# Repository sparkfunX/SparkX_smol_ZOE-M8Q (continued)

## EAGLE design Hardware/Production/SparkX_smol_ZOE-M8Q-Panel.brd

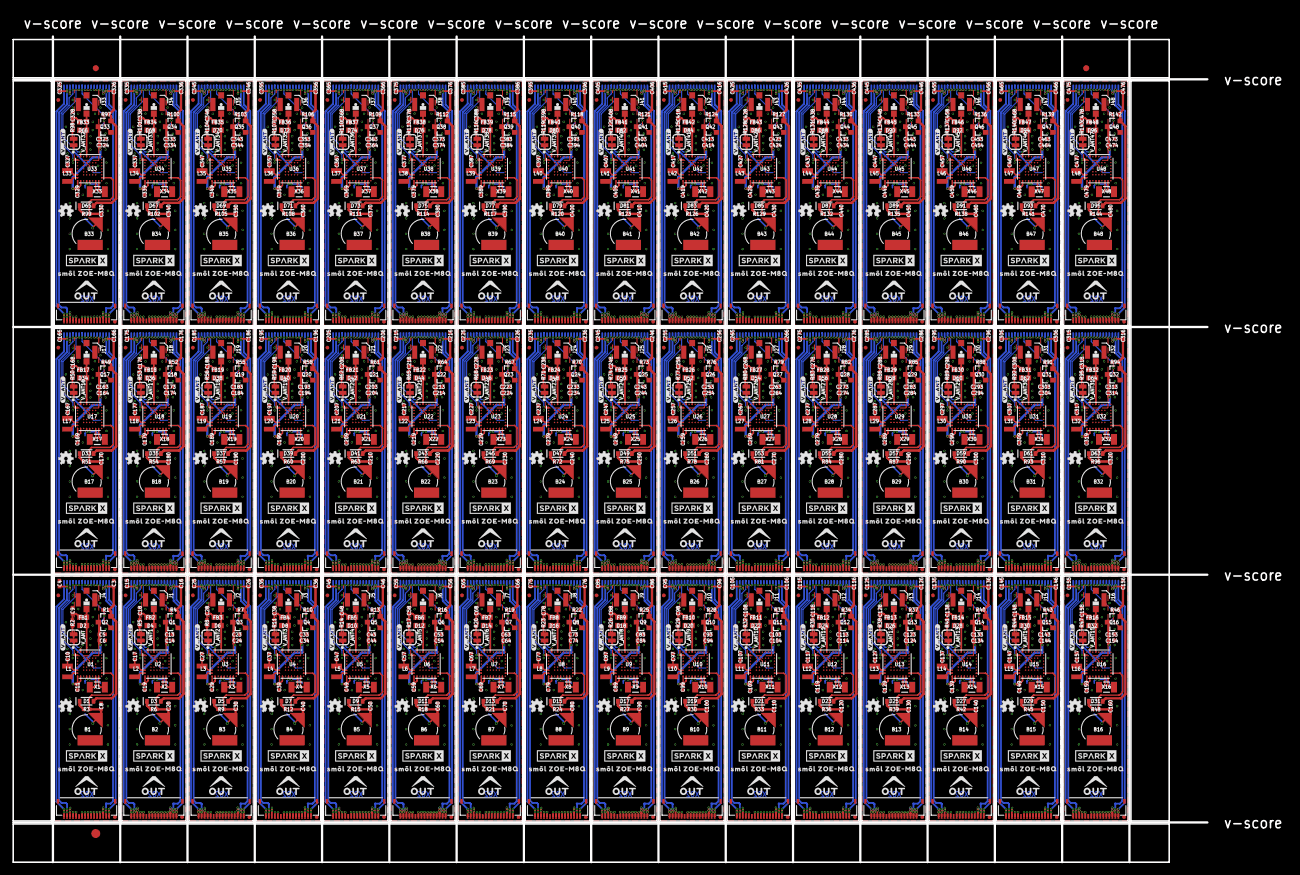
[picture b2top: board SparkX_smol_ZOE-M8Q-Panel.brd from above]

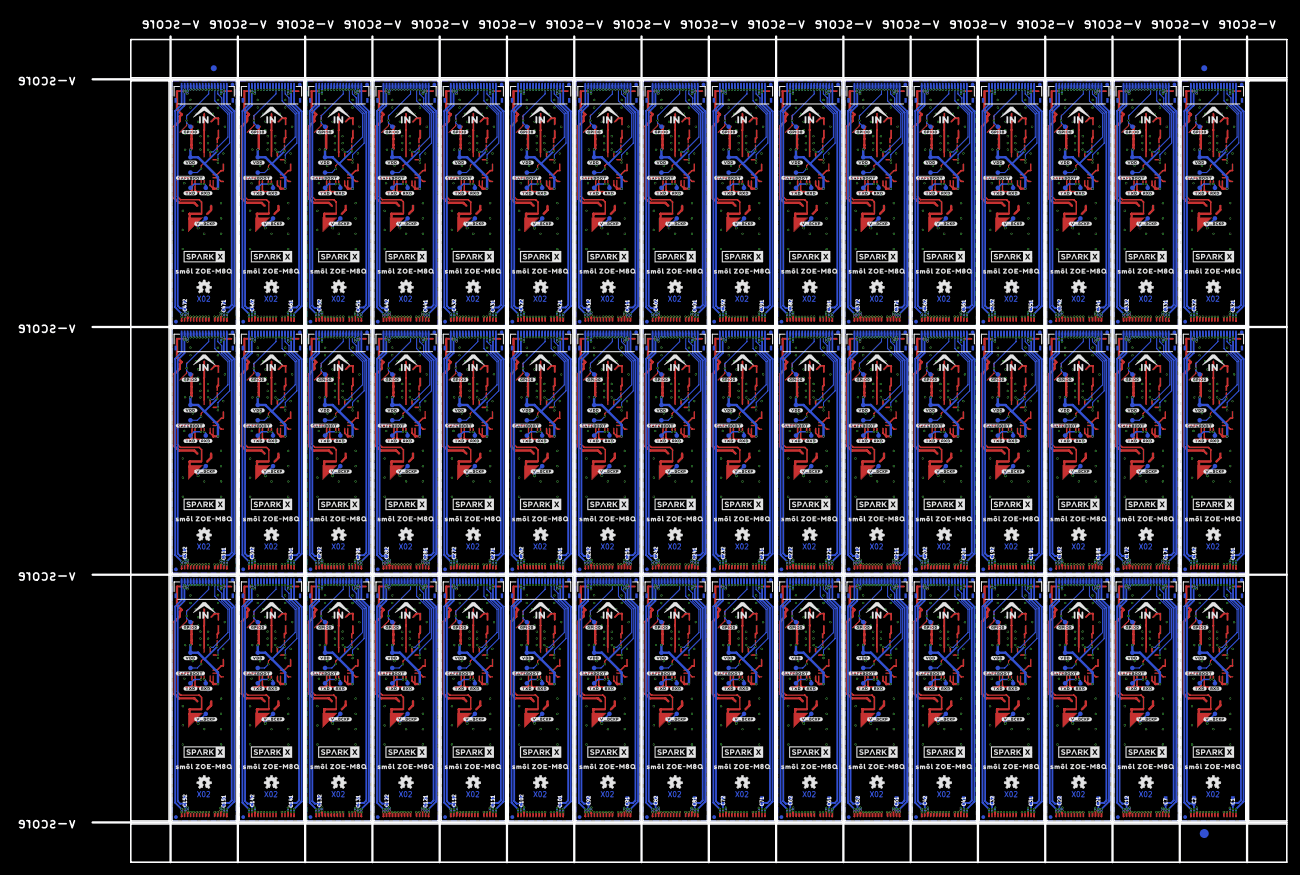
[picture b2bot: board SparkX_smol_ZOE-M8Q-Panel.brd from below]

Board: 4 copper layers, 198.4 x 137.2 mm, 2502 parts (1059 on the bottom side), 1296 nets.

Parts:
!SAFEBOOT!, !SAFEBOOT!1, !SAFEBOOT!2, !SAFEBOOT!3, !SAFEBOOT!4, !SAFEBOOT!5, !SAFEBOOT!6, !SAFEBOOT!7, !SAFEBOOT!8, !SAFEBOOT!9, !SAFEBOOT!10, !SAFEBOOT!11, !SAFEBOOT!12, !SAFEBOOT!13, !SAFEBOOT!14, !SAFEBOOT!15, !SAFEBOOT!16, !SAFEBOOT!17, !SAFEBOOT!18, !SAFEBOOT!19, !SAFEBOOT!20, !SAFEBOOT!21, !SAFEBOOT!22, !SAFEBOOT!23, !SAFEBOOT!24, !SAFEBOOT!25, !SAFEBOOT!26, !SAFEBOOT!27, !SAFEBOOT!28, !SAFEBOOT!29, !SAFEBOOT!30, !SAFEBOOT!31, !SAFEBOOT!32, !SAFEBOOT!33, !SAFEBOOT!34, !SAFEBOOT!35, !SAFEBOOT!36, !SAFEBOOT!37, !SAFEBOOT!38, !SAFEBOOT!39, !SAFEBOOT!40, !SAFEBOOT!41, !SAFEBOOT!42, !SAFEBOOT!43, !SAFEBOOT!44, !SAFEBOOT!45, !SAFEBOOT!46, !SAFEBOOT!47: TEST-POINT3; PAD.03X.03
B1, B2, B3, B4, B5, B6, B7, B8, B9, B10, B11, B12, B13, B14, B15, B16, B17, B18, B19, B20, B21, B22, B23, B24, B25, B26, B27, B28, B29, B30, B31, B32, B33, B34, B35, B36, B37, B38, B39, B40, B41, B42, B43, B44, B45, B46, B47, B48: 6.8MM_COIN_CELL; ML414H_IV01E
C1, C2, C3, C4, C5, C7, C12, C13, C15, C16, C21, C22, C23, C25, C26, C31, C32, C33, C35, C36, C41, C42, C43, C45, C46, C51, C52, C53, C55, C56, C61, C62, C63, C65, C66, C71, C72, C73, C75, C76, C81, C82, C83, C85, C86, C91, C92, C93, C95, C96, C101, C102, C103, C105, C106, C111, C112, C113, C115, C116, C121, C122, C123, C125, C126, C131, C132, C133, C135, C136, C141, C142, C143, C145, C146, C151, C152, C153, C155, C156, C161, C162, C163, C165, C166, C171, C172, C173, C175, C176, C181, C182, C183, C185, C186, C191, C192, C193, C195, C196, C201, C202, C203, C205, C206, C211, C212, C213, C215, C216, C221, C222, C223, C225, C226, C231, C232, C233, C235, C236, C241, C242, C243, C245, C246, C251, C252, C253, C255, C256, C261, C262, C263, C265, C266, C271, C272, C273, C275, C276, C281, C282, C283, C285, C286, C291, C292, C293, C295, C296, C301, C302, C303, C305, C306, C311, C312, C313, C315, C316, C321, C322, C323, C325, C326, C331, C332, C333, C335, C336, C341, C342, C343, C345, C346, C351, C352, C353, C355, C356, C361, C362, C363, C365, C366, C371, C372, C373, C375, C376, C381, C382, C383, C385, C386, C391, C392, C393, C395, C396, C401, C402, C403, C405, C406, C411, C412, C413, C415, C416, C421, C422, C423, C425, C426, C431, C432, C433, C435, C436, C441, C442, C443, C445, C446, C451, C452, C453, C455, C456, C461, C462, C463, C465, C466, C471, C472, C473, C475, C476: 2.2uF; 0402-TIGHT
C6, C11, C14, C19, C24, C29, C34, C39, C44, C49, C54, C59, C64, C69, C74, C79, C84, C89, C94, C99, C104, C109, C114, C119, C124, C129, C134, C139, C144, C149, C154, C159, C164, C169, C174, C179, C184, C189, C194, C199, C204, C209, C214, C219, C224, C229, C234, C239, C244, C249, C254, C259, C264, C269, C274, C279, C284, C289, C294, C299, C304, C309, C314, C319, C324, C329, C334, C339, C344, C349, C354, C359, C364, C369, C374, C379, C384, C389, C394, C399, C404, C409, C414, C419, C424, C429, C434, C439, C444, C449, C454, C459, C464, C469, C474, C479: 0.1uF; 0402-TIGHT
C8, C20, C30, C40, C50, C60, C70, C80, C90, C100, C110, C120, C130, C140, C150, C160, C170, C180, C190, C200, C210, C220, C230, C240, C250, C260, C270, C280, C290, C300, C310, C320, C330, C340, C350, C360, C370, C380, C390, C400, C410, C420, C430, C440, C450, C460, C470, C480: 1.0uF; 0402-TIGHT
C9, C18, C28, C38, C48, C58, C68, C78, C88, C98, C108, C118, C128, C138, C148, C158, C168, C178, C188, C198, C208, C218, C228, C238, C248, C258, C268, C278, C288, C298, C308, C318, C328, C338, C348, C358, C368, C378, C388, C398, C408, C418, C428, C438, C448, C458, C468, C478: 47PF-0402_TIGHT-25V-5%-X7R; 0402-TIGHT
C10, C17, C27, C37, C47, C57, C67, C77, C87, C97, C107, C117, C127, C137, C147, C157, C167, C177, C187, C197, C207, C217, C227, C237, C247, C257, C267, C277, C287, C297, C307, C317, C327, C337, C347, C357, C367, C377, C387, C397, C407, C417, C427, C437, C447, C457, C467, C477: 4.7uF; 0402-TIGHT
D1, D3, D5, D7, D9, D11, D13, D15, D17, D19, D21, D23, D25, D27, D29, D31, D33, D35, D37, D39, D41, D43, D45, D47, D49, D51, D53, D55, D57, D59, D61, D63, D65, D67, D69, D71, D73, D75, D77, D79, D81, D83, D85, D87, D89, D91, D93, D95: 1A/23V/620mV; SOD-323
D2, D4, D6, D8, D10, D12, D14, D16, D18, D20, D22, D24, D26, D28, D30, D32, D34, D36, D38, D40, D42, D44, D46, D48, D50, D52, D54, D56, D58, D60, D62, D64, D66, D68, D70, D72, D74, D76, D78, D80, D82, D84, D86, D88, D90, D92, D94, D96: PESD0402; 0402
E$1, E$2, E$3, E$4: FIDUCIAL-1X2
E$5, E$6: FIDUCIAL-1.5X3
FB1, FB2, FB3, FB4, FB5, FB6, FB7, FB8, FB9, FB10, FB11, FB12, FB13, FB14, FB15, FB16, FB17, FB18, FB19, FB20, FB21, FB22, FB23, FB24, FB25, FB26, FB27, FB28, FB29, FB30, FB31, FB32, FB33, FB34, FB35, FB36, FB37, FB38, FB39, FB40, FB41, FB42, FB43, FB44, FB45, FB46, FB47, FB48: FERRITE_BEAD-120_OHM-0402; 0402
FD1, FD2, FD3, FD4, FD5, FD6, FD7, FD8, FD9, FD10, FD11, FD12, FD13, FD14, FD15, FD16, FD17, FD18, FD19, FD20, FD21, FD22, FD23, FD24, FD25, FD26, FD27, FD28, FD29, FD30, FD31, FD32, FD33, FD34, FD35, FD36, FD37, FD38, FD39, FD40, FD41, FD42, FD43, FD44, FD45, FD46, FD47, FD48, FD49, FD50, FD51, FD52, FD53, FD54, FD55, FD56, FD57, FD58, FD59, FD60, FD61, FD62, FD63, FD64, FD65, FD66, FD67, FD68, FD69, FD70, FD71, FD72, FD73, FD74, FD75, FD76, FD77, FD78, FD79, FD80, FD81, FD82, FD83, FD84, FD85, FD86, FD87, FD88, FD89, FD90, FD91, FD92, FD93, FD94, FD95, FD96, FD97, FD98, FD99, FD100, FD101, FD102, FD103, FD104, FD105, FD106, FD107, FD108, FD109, FD110, FD111, FD112, FD113, FD114, FD115, FD116, FD117, FD118, FD119, FD120, FD121, FD122, FD123, FD124, FD125, FD126, FD127, FD128, FD129, FD130, FD131, FD132, FD133, FD134, FD135, FD136, FD137, FD138, FD139, FD140, FD141, FD142, FD143, FD144, FD145, FD146, FD147, FD148, FD149, FD150, FD151, FD152, FD153, FD154, FD155, FD156, FD157, FD158, FD159, FD160, FD161, FD162, FD163, FD164, FD165, FD166, FD167, FD168, FD169, FD170, FD171, FD172, FD173, FD174, FD175, FD176, FD177, FD178, FD179, FD180, FD181, FD182, FD183, FD184, FD185, FD186, FD187, FD188, FD189, FD190, FD191, FD192: FIDUCIALUFIDUCIAL; FIDUCIAL-MICRO
GPIO0, GPIO1, GPIO2, GPIO3, GPIO4, GPIO5, GPIO6, GPIO7, GPIO8, GPIO9, GPIO10, GPIO11, GPIO12, GPIO13, GPIO14, GPIO15, GPIO16, GPIO17, GPIO18, GPIO19, GPIO20, GPIO21, GPIO22, GPIO23, GPIO24, GPIO25, GPIO26, GPIO27, GPIO28, GPIO29, GPIO30, GPIO31, GPIO32, GPIO33, GPIO34, GPIO35, GPIO36, GPIO37, GPIO38, GPIO39, GPIO40, GPIO41, GPIO42, GPIO43, GPIO44, GPIO45, GPIO46, GPIO47: TEST-POINT3; PAD.03X.03
IN, IN1, IN2, IN3, IN4, IN5, IN6, IN7, IN8, IN9, IN10, IN11, IN12, IN13, IN14, IN15, IN16, IN17, IN18, IN19, IN20, IN21, IN22, IN23, IN24, IN25, IN26, IN27, IN28, IN29, IN30, IN31, IN32, IN33, IN34, IN35, IN36, IN37, IN38, IN39, IN40, IN41, IN42, IN43, IN44, IN45, IN46, IN47: FPC_16_0.5MM
J1, J2, J3, J4, J5, J6, J7, J8, J9, J10, J11, J12, J13, J14, J15, J16, J17, J18, J19, J20, J21, J22, J23, J24, J25, J26, J27, J28, J29, J30, J31, J32, J33, J34, J35, J36, J37, J38, J39, J40, J41, J42, J43, J44, J45, J46, J47, J48: U.FL
L1, L2, L3, L4, L5, L6, L7, L8, L9, L10, L11, L12, L13, L14, L15, L16, L17, L18, L19, L20, L21, L22, L23, L24, L25, L26, L27, L28, L29, L30, L31, L32, L33, L34, L35, L36, L37, L38, L39, L40, L41, L42, L43, L44, L45, L46, L47, L48: 2.2uH; 0806
LOGO1, LOGO2, LOGO3, LOGO4, LOGO5, LOGO6, LOGO7, LOGO8, LOGO9, LOGO10, LOGO11, LOGO12, LOGO13, LOGO14, LOGO15, LOGO16, LOGO17, LOGO18, LOGO19, LOGO20, LOGO21, LOGO22, LOGO23, LOGO24, LOGO25, LOGO26, LOGO27, LOGO28, LOGO29, LOGO30, LOGO31, LOGO32, LOGO33, LOGO34, LOGO35, LOGO36, LOGO37, LOGO38, LOGO39, LOGO40, LOGO41, LOGO42, LOGO43, LOGO44, LOGO45, LOGO46, LOGO47, LOGO48, LOGO49, LOGO50, LOGO51, LOGO52, LOGO53, LOGO54, LOGO55, LOGO56, LOGO57, LOGO58, LOGO59, LOGO60, LOGO61, LOGO62, LOGO63, LOGO64, LOGO65, LOGO66, LOGO67, LOGO68, LOGO69, LOGO70, LOGO71, LOGO72, LOGO73, LOGO74, LOGO75, LOGO76, LOGO77, LOGO78, LOGO79, LOGO80, LOGO81, LOGO82, LOGO83, LOGO84, LOGO85, LOGO86, LOGO87, LOGO88, LOGO89, LOGO90, LOGO91, LOGO92, LOGO93, LOGO94, LOGO95, LOGO96: OSHW-LOGOMINI; OSHW-LOGO-MINI
OUT, OUT1, OUT2, OUT3, OUT4, OUT5, OUT6, OUT7, OUT8, OUT9, OUT10, OUT11, OUT12, OUT13, OUT14, OUT15, OUT16, OUT17, OUT18, OUT19, OUT20, OUT21, OUT22, OUT23, OUT24, OUT25, OUT26, OUT27, OUT28, OUT29, OUT30, OUT31, OUT32, OUT33, OUT34, OUT35, OUT36, OUT37, OUT38, OUT39, OUT40, OUT41, OUT42, OUT43, OUT44, OUT45, OUT46, OUT47: FPC_16_0.5MM
Q1, Q2, Q3, Q4, Q5, Q6, Q7, Q8, Q9, Q10, Q11, Q12, Q13, Q14, Q15, Q16, Q17, Q18, Q19, Q20, Q21, Q22, Q23, Q24, Q25, Q26, Q27, Q28, Q29, Q30, Q31, Q32, Q33, Q34, Q35, Q36, Q37, Q38, Q39, Q40, Q41, Q42, Q43, Q44, Q45, Q46, Q47, Q48: 20V/4.2A/52mΩ/1.4W; SOT23-3
R1, R4, R7, R10, R13, R16, R19, R22, R25, R28, R31, R34, R37, R40, R43, R46, R49, R52, R55, R58, R61, R64, R67, R70, R73, R76, R79, R82, R85, R88, R91, R94, R97, R100, R103, R106, R109, R112, R115, R118, R121, R124, R127, R130, R133, R136, R139, R142: 100k; 0402-TIGHT
R2, R5, R8, R11, R14, R17, R20, R23, R26, R29, R32, R35, R38, R41, R44, R47, R50, R53, R56, R59, R62, R65, R68, R71, R74, R77, R80, R83, R86, R89, R92, R95, R98, R101, R104, R107, R110, R113, R116, R119, R122, R125, R128, R131, R134, R137, R140, R143: 2; 0402-TIGHT
R3, R6, R9, R12, R15, R18, R21, R24, R27, R30, R33, R36, R39, R42, R45, R48, R51, R54, R57, R60, R63, R66, R69, R72, R75, R78, R81, R84, R87, R90, R93, R96, R99, R102, R105, R108, R111, R114, R117, R120, R123, R126, R129, R132, R135, R138, R141, R144: 1k; 0402-TIGHT
RXD, RXD1, RXD2, RXD3, RXD4, RXD5, RXD6, RXD7, RXD8, RXD9, RXD10, RXD11, RXD12, RXD13, RXD14, RXD15, RXD16, RXD17, RXD18, RXD19, RXD20, RXD21, RXD22, RXD23, RXD24, RXD25, RXD26, RXD27, RXD28, RXD29, RXD30, RXD31, RXD32, RXD33, RXD34, RXD35, RXD36, RXD37, RXD38, RXD39, RXD40, RXD41, RXD42, RXD43, RXD44, RXD45, RXD46, RXD47: TEST-POINT3; PAD.03X.03
TXD, TXD1, TXD2, TXD3, TXD4, TXD5, TXD6, TXD7, TXD8, TXD9, TXD10, TXD11, TXD12, TXD13, TXD14, TXD15, TXD16, TXD17, TXD18, TXD19, TXD20, TXD21, TXD22, TXD23, TXD24, TXD25, TXD26, TXD27, TXD28, TXD29, TXD30, TXD31, TXD32, TXD33, TXD34, TXD35, TXD36, TXD37, TXD38, TXD39, TXD40, TXD41, TXD42, TXD43, TXD44, TXD45, TXD46, TXD47: TEST-POINT3; PAD.03X.03
U1, U2, U3, U4, U5, U6, U7, U8, U9, U10, U11, U12, U13, U14, U15, U16, U17, U18, U19, U20, U21, U22, U23, U24, U25, U26, U27, U28, U29, U30, U31, U32, U33, U34, U35, U36, U37, U38, U39, U40, U41, U42, U43, U44, U45, U46, U47, U48: U-BLOX_ZOE_M8Q-0-10; UBLOX_ZOE_M8-0-10
U$1, U$4, U$16, U$17, U$31, U$32, U$46, U$47, U$61, U$62, U$76, U$77, U$91, U$92, U$106, U$107, U$121, U$122, U$136, U$137, U$151, U$152, U$166, U$167, U$181, U$182, U$196, U$197, U$211, U$212, U$226, U$227, U$241, U$242, U$256, U$257, U$271, U$272, U$286, U$287, U$301, U$302, U$316, U$317, U$331, U$332, U$346, U$347, U$361, U$362, U$376, U$377, U$391, U$392, U$406, U$407, U$421, U$422, U$436, U$437, U$451, U$452, U$466, U$467, U$481, U$482, U$496, U$497, U$511, U$512, U$526, U$527, U$541, U$542, U$556, U$557, U$571, U$572, U$586, U$587, U$601, U$602, U$616, U$617, U$631, U$632, U$646, U$647, U$661, U$662, U$676, U$677, U$691, U$692, U$706, U$707: SPARKX-LOGO3; SPARKX-SMALL
U$2, U$12, U$27, U$28, U$42, U$43, U$57, U$58, U$72, U$73, U$87, U$88, U$102, U$103, U$117, U$118, U$132, U$133, U$147, U$148, U$162, U$163, U$177, U$178, U$192, U$193, U$207, U$208, U$222, U$223, U$237, U$238, U$252, U$253, U$267, U$268, U$282, U$283, U$297, U$298, U$312, U$313, U$327, U$328, U$342, U$343, U$357, U$358, U$372, U$373, U$387, U$388, U$402, U$403, U$417, U$418, U$432, U$433, U$447, U$448, U$462, U$463, U$477, U$478, U$492, U$493, U$507, U$508, U$522, U$523, U$537, U$538, U$552, U$553, U$567, U$568, U$582, U$583, U$597, U$598, U$612, U$613, U$627, U$628, U$642, U$643, U$657, U$658, U$672, U$673, U$687, U$688, U$702, U$703, U$717, U$718: SM�L_ZOE#M8Q0
U$3, U$13, U$29, U$30, U$44, U$45, U$59, U$60, U$74, U$75, U$89, U$90, U$104, U$105, U$119, U$120, U$134, U$135, U$149, U$150, U$164, U$165, U$179, U$180, U$194, U$195, U$209, U$210, U$224, U$225, U$239, U$240, U$254, U$255, U$269, U$270, U$284, U$285, U$299, U$300, U$314, U$315, U$329, U$330, U$344, U$345, U$359, U$360, U$374, U$375, U$389, U$390, U$404, U$405, U$419, U$420, U$434, U$435, U$449, U$450, U$464, U$465, U$479, U$480, U$494, U$495, U$509, U$510, U$524, U$525, U$539, U$540, U$554, U$555, U$569, U$570, U$584, U$585, U$599, U$600, U$614, U$615, U$629, U$630, U$644, U$645, U$659, U$660, U$674, U$675, U$689, U$690, U$704, U$705, U$719, U$720: SMOL_LOGOSMALL; SMOL_SMALL
U$5, U$18, U$33, U$48, U$63, U$78, U$93, U$108, U$123, U$138, U$153, U$168, U$183, U$198, U$213, U$228, U$243, U$258, U$273, U$288, U$303, U$318, U$333, U$348, U$363, U$378, U$393, U$408, U$423, U$438, U$453, U$468, U$483, U$498, U$513, U$528, U$543, U$558, U$573, U$588, U$603, U$618, U$633, U$648, U$663, U$678, U$693, U$708: #V_ANT#0
U$6, U$19, U$34, U$49, U$64, U$79, U$94, U$109, U$124, U$139, U$154, U$169, U$184, U$199, U$214, U$229, U$244, U$259, U$274, U$289, U$304, U$319, U$334, U$349, U$364, U$379, U$394, U$409, U$424, U$439, U$454, U$469, U$484, U$499, U$514, U$529, U$544, U$559, U$574, U$589, U$604, U$619, U$634, U$649, U$664, U$679, U$694, U$709: #VDD#0
U$7, U$20, U$35, U$50, U$65, U$80, U$95, U$110, U$125, U$140, U$155, U$170, U$185, U$200, U$215, U$230, U$245, U$260, U$275, U$290, U$305, U$320, U$335, U$350, U$365, U$380, U$395, U$410, U$425, U$440, U$455, U$470, U$485, U$500, U$515, U$530, U$545, U$560, U$575, U$590, U$605, U$620, U$635, U$650, U$665, U$680, U$695, U$710: ##SAFEBOOT##0
U$8, U$21, U$36, U$51, U$66, U$81, U$96, U$111, U$126, U$141, U$156, U$171, U$186, U$201, U$216, U$231, U$246, U$261, U$276, U$291, U$306, U$321, U$336, U$351, U$366, U$381, U$396, U$411, U$426, U$441, U$456, U$471, U$486, U$501, U$516, U$531, U$546, U$561, U$576, U$591, U$606, U$621, U$636, U$651, U$666, U$681, U$696, U$711: #TXD#0
U$9, U$22, U$37, U$52, U$67, U$82, U$97, U$112, U$127, U$142, U$157, U$172, U$187, U$202, U$217, U$232, U$247, U$262, U$277, U$292, U$307, U$322, U$337, U$352, U$367, U$382, U$397, U$412, U$427, U$442, U$457, U$472, U$487, U$502, U$517, U$532, U$547, U$562, U$577, U$592, U$607, U$622, U$637, U$652, U$667, U$682, U$697, U$712: #RXD#0
U$10, U$23, U$38, U$53, U$68, U$83, U$98, U$113, U$128, U$143, U$158, U$173, U$188, U$203, U$218, U$233, U$248, U$263, U$278, U$293, U$308, U$323, U$338, U$353, U$368, U$383, U$398, U$413, U$428, U$443, U$458, U$473, U$488, U$503, U$518, U$533, U$548, U$563, U$578, U$593, U$608, U$623, U$638, U$653, U$668, U$683, U$698, U$713: #GPIO0#0
U$11, U$24, U$39, U$54, U$69, U$84, U$99, U$114, U$129, U$144, U$159, U$174, U$189, U$204, U$219, U$234, U$249, U$264, U$279, U$294, U$309, U$324, U$339, U$354, U$369, U$384, U$399, U$414, U$429, U$444, U$459, U$474, U$489, U$504, U$519, U$534, U$549, U$564, U$579, U$594, U$609, U$624, U$639, U$654, U$669, U$684, U$699, U$714: #V_BCKP#0
U$14, U$25, U$40, U$55, U$70, U$85, U$100, U$115, U$130, U$145, U$160, U$175, U$190, U$205, U$220, U$235, U$250, U$265, U$280, U$295, U$310, U$325, U$340, U$355, U$370, U$385, U$400, U$415, U$430, U$445, U$460, U$475, U$490, U$505, U$520, U$535, U$550, U$565, U$580, U$595, U$610, U$625, U$640, U$655, U$670, U$685, U$700, U$715: OUT0
U$15, U$26, U$41, U$56, U$71, U$86, U$101, U$116, U$131, U$146, U$161, U$176, U$191, U$206, U$221, U$236, U$251, U$266, U$281, U$296, U$311, U$326, U$341, U$356, U$371, U$386, U$401, U$416, U$431, U$446, U$461, U$476, U$491, U$506, U$521, U$536, U$551, U$566, U$581, U$596, U$611, U$626, U$641, U$656, U$671, U$686, U$701, U$716: IN0
VDD, VDD1, VDD2, VDD3, VDD4, VDD5, VDD6, VDD7, VDD8, VDD9, VDD10, VDD11, VDD12, VDD13, VDD14, VDD15, VDD16, VDD17, VDD18, VDD19, VDD20, VDD21, VDD22, VDD23, VDD24, VDD25, VDD26, VDD27, VDD28, VDD29, VDD30, VDD31, VDD32, VDD33, VDD34, VDD35, VDD36, VDD37, VDD38, VDD39, VDD40, VDD41, VDD42, VDD43, VDD44, VDD45, VDD46, VDD47: TEST-POINT3; PAD.03X.03
V_ANT, V_ANT1, V_ANT2, V_ANT3, V_ANT4, V_ANT5, V_ANT6, V_ANT7, V_ANT8, V_ANT9, V_ANT10, V_ANT11, V_ANT12, V_ANT13, V_ANT14, V_ANT15, V_ANT16, V_ANT17, V_ANT18, V_ANT19, V_ANT20, V_ANT21, V_ANT22, V_ANT23, V_ANT24, V_ANT25, V_ANT26, V_ANT27, V_ANT28, V_ANT29, V_ANT30, V_ANT31, V_ANT32, V_ANT33, V_ANT34, V_ANT35, V_ANT36, V_ANT37, V_ANT38, V_ANT39, V_ANT40, V_ANT41, V_ANT42, V_ANT43, V_ANT44, V_ANT45, V_ANT46, V_ANT47: JUMPER-SMT_2_NC_TRACE_SILK; SMT-JUMPER_2_NC_TRACE_SILK
V_BCKP, V_BCKP1, V_BCKP2, V_BCKP3, V_BCKP4, V_BCKP5, V_BCKP6, V_BCKP7, V_BCKP8, V_BCKP9, V_BCKP10, V_BCKP11, V_BCKP12, V_BCKP13, V_BCKP14, V_BCKP15, V_BCKP16, V_BCKP17, V_BCKP18, V_BCKP19, V_BCKP20, V_BCKP21, V_BCKP22, V_BCKP23, V_BCKP24, V_BCKP25, V_BCKP26, V_BCKP27, V_BCKP28, V_BCKP29, V_BCKP30, V_BCKP31, V_BCKP32, V_BCKP33, V_BCKP34, V_BCKP35, V_BCKP36, V_BCKP37, V_BCKP38, V_BCKP39, V_BCKP40, V_BCKP41, V_BCKP42, V_BCKP43, V_BCKP44, V_BCKP45, V_BCKP46, V_BCKP47: TEST-POINT3; PAD.03X.03
X1, X2, X3, X4, X5, X6, X7, X8, X9, X10, X11, X12, X13, X14, X15, X16, X17, X18, X19, X20, X21, X22, X23, X24, X25, X26, X27, X28, X29, X30, X31, X32, X33, X34, X35, X36, X37, X38, X39, X40, X41, X42, X43, X44, X45, X46, X47, X48: 32.768kHz; CRYSTAL-SMD-3.2X1.5MM

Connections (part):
3.3V: C1.1, C2.1, C3.1, C4.1, D1.A, IN.2, IN.15, OUT.2, OUT.15, Q2.2, R1.2
3.3V1: C7.1, C12.1, C15.1, C16.1, D3.A, IN1.2, IN1.15, OUT1.2, OUT1.15, Q1.2, R4.2
3.3V2: C21.1, C22.1, C25.1, C26.1, D5.A, IN2.2, IN2.15, OUT2.2, OUT2.15, Q3.2, R7.2
3.3V3: C31.1, C32.1, C35.1, C36.1, D7.A, IN3.2, IN3.15, OUT3.2, OUT3.15, Q4.2, R10.2
3.3V4: C41.1, C42.1, C45.1, C46.1, D9.A, IN4.2, IN4.15, OUT4.2, OUT4.15, Q5.2, R13.2
3.3V5: C51.1, C52.1, C55.1, C56.1, D11.A, IN5.2, IN5.15, OUT5.2, OUT5.15, Q6.2, R16.2
3.3V6: C61.1, C62.1, C65.1, C66.1, D13.A, IN6.2, IN6.15, OUT6.2, OUT6.15, Q7.2, R19.2
3.3V7: C71.1, C72.1, C75.1, C76.1, D15.A, IN7.2, IN7.15, OUT7.2, OUT7.15, Q8.2, R22.2
3.3V8: C81.1, C82.1, C85.1, C86.1, D17.A, IN8.2, IN8.15, OUT8.2, OUT8.15, Q9.2, R25.2
3.3V9: C91.1, C92.1, C95.1, C96.1, D19.A, IN9.2, IN9.15, OUT9.2, OUT9.15, Q10.2, R28.2
3.3V10: C101.1, C102.1, C105.1, C106.1, D21.A, IN10.2, IN10.15, OUT10.2, OUT10.15, Q11.2, R31.2
3.3V11: C111.1, C112.1, C115.1, C116.1, D23.A, IN11.2, IN11.15, OUT11.2, OUT11.15, Q12.2, R34.2
3.3V12: C121.1, C122.1, C125.1, C126.1, D25.A, IN12.2, IN12.15, OUT12.2, OUT12.15, Q13.2, R37.2
3.3V13: C131.1, C132.1, C135.1, C136.1, D27.A, IN13.2, IN13.15, OUT13.2, OUT13.15, Q14.2, R40.2
3.3V14: C141.1, C142.1, C145.1, C146.1, D29.A, IN14.2, IN14.15, OUT14.2, OUT14.15, Q15.2, R43.2
3.3V15: C151.1, C152.1, C155.1, C156.1, D31.A, IN15.2, IN15.15, OUT15.2, OUT15.15, Q16.2, R46.2
3.3V16: C161.1, C162.1, C165.1, C166.1, D33.A, IN16.2, IN16.15, OUT16.2, OUT16.15, Q17.2, R49.2
3.3V17: C171.1, C172.1, C175.1, C176.1, D35.A, IN17.2, IN17.15, OUT17.2, OUT17.15, Q18.2, R52.2
3.3V18: C181.1, C182.1, C185.1, C186.1, D37.A, IN18.2, IN18.15, OUT18.2, OUT18.15, Q19.2, R55.2
3.3V19: C191.1, C192.1, C195.1, C196.1, D39.A, IN19.2, IN19.15, OUT19.2, OUT19.15, Q20.2, R58.2
3.3V20: C201.1, C202.1, C205.1, C206.1, D41.A, IN20.2, IN20.15, OUT20.2, OUT20.15, Q21.2, R61.2
3.3V21: C211.1, C212.1, C215.1, C216.1, D43.A, IN21.2, IN21.15, OUT21.2, OUT21.15, Q22.2, R64.2
3.3V22: C221.1, C222.1, C225.1, C226.1, D45.A, IN22.2, IN22.15, OUT22.2, OUT22.15, Q23.2, R67.2
3.3V23: C231.1, C232.1, C235.1, C236.1, D47.A, IN23.2, IN23.15, OUT23.2, OUT23.15, Q24.2, R70.2
3.3V24: C241.1, C242.1, C245.1, C246.1, D49.A, IN24.2, IN24.15, OUT24.2, OUT24.15, Q25.2, R73.2
3.3V25: C251.1, C252.1, C255.1, C256.1, D51.A, IN25.2, IN25.15, OUT25.2, OUT25.15, Q26.2, R76.2
3.3V26: C261.1, C262.1, C265.1, C266.1, D53.A, IN26.2, IN26.15, OUT26.2, OUT26.15, Q27.2, R79.2
3.3V27: C271.1, C272.1, C275.1, C276.1, D55.A, IN27.2, IN27.15, OUT27.2, OUT27.15, Q28.2, R82.2
3.3V28: C281.1, C282.1, C285.1, C286.1, D57.A, IN28.2, IN28.15, OUT28.2, OUT28.15, Q29.2, R85.2
3.3V29: C291.1, C292.1, C295.1, C296.1, D59.A, IN29.2, IN29.15, OUT29.2, OUT29.15, Q30.2, R88.2
3.3V30: C301.1, C302.1, C305.1, C306.1, D61.A, IN30.2, IN30.15, OUT30.2, OUT30.15, Q31.2, R91.2
3.3V31: C311.1, C312.1, C315.1, C316.1, D63.A, IN31.2, IN31.15, OUT31.2, OUT31.15, Q32.2, R94.2
3.3V32: C321.1, C322.1, C325.1, C326.1, D65.A, IN32.2, IN32.15, OUT32.2, OUT32.15, Q33.2, R97.2
3.3V33: C331.1, C332.1, C335.1, C336.1, D67.A, IN33.2, IN33.15, OUT33.2, OUT33.15, Q34.2, R100.2
3.3V34: C341.1, C342.1, C345.1, C346.1, D69.A, IN34.2, IN34.15, OUT34.2, OUT34.15, Q35.2, R103.2
3.3V35: C351.1, C352.1, C355.1, C356.1, D71.A, IN35.2, IN35.15, OUT35.2, OUT35.15, Q36.2, R106.2
3.3V36: C361.1, C362.1, C365.1, C366.1, D73.A, IN36.2, IN36.15, OUT36.2, OUT36.15, Q37.2, R109.2
3.3V37: C371.1, C372.1, C375.1, C376.1, D75.A, IN37.2, IN37.15, OUT37.2, OUT37.15, Q38.2, R112.2
3.3V38: C381.1, C382.1, C385.1, C386.1, D77.A, IN38.2, IN38.15, OUT38.2, OUT38.15, Q39.2, R115.2
3.3V39: C391.1, C392.1, C395.1, C396.1, D79.A, IN39.2, IN39.15, OUT39.2, OUT39.15, Q40.2, R118.2
3.3V40: C401.1, C402.1, C405.1, C406.1, D81.A, IN40.2, IN40.15, OUT40.2, OUT40.15, Q41.2, R121.2
3.3V41: C411.1, C412.1, C415.1, C416.1, D83.A, IN41.2, IN41.15, OUT41.2, OUT41.15, Q42.2, R124.2
3.3V42: C421.1, C422.1, C425.1, C426.1, D85.A, IN42.2, IN42.15, OUT42.2, OUT42.15, Q43.2, R127.2
3.3V43: C431.1, C432.1, C435.1, C436.1, D87.A, IN43.2, IN43.15, OUT43.2, OUT43.15, Q44.2, R130.2
3.3V44: C441.1, C442.1, C445.1, C446.1, D89.A, IN44.2, IN44.15, OUT44.2, OUT44.15, Q45.2, R133.2
3.3V45: C451.1, C452.1, C455.1, C456.1, D91.A, IN45.2, IN45.15, OUT45.2, OUT45.15, Q46.2, R136.2
3.3V46: C461.1, C462.1, C465.1, C466.1, D93.A, IN46.2, IN46.15, OUT46.2, OUT46.15, Q47.2, R139.2
3.3V47: C471.1, C472.1, C475.1, C476.1, D95.A, IN47.2, IN47.15, OUT47.2, OUT47.15, Q48.2, R142.2
!SAFEBOOT!: !SAFEBOOT!.1, U1.34
!SAFEBOOT!1: !SAFEBOOT!1.1, U2.34
!SAFEBOOT!2: !SAFEBOOT!2.1, U3.34
!SAFEBOOT!3: !SAFEBOOT!3.1, U4.34
!SAFEBOOT!4: !SAFEBOOT!4.1, U5.34
!SAFEBOOT!5: !SAFEBOOT!5.1, U6.34
!SAFEBOOT!6: !SAFEBOOT!6.1, U7.34
!SAFEBOOT!7: !SAFEBOOT!7.1, U8.34
!SAFEBOOT!8: !SAFEBOOT!8.1, U9.34
!SAFEBOOT!9: !SAFEBOOT!9.1, U10.34
!SAFEBOOT!10: !SAFEBOOT!10.1, U11.34
!SAFEBOOT!11: !SAFEBOOT!11.1, U12.34
!SAFEBOOT!12: !SAFEBOOT!12.1, U13.34
!SAFEBOOT!13: !SAFEBOOT!13.1, U14.34
!SAFEBOOT!14: !SAFEBOOT!14.1, U15.34
!SAFEBOOT!15: !SAFEBOOT!15.1, U16.34
!SAFEBOOT!16: !SAFEBOOT!16.1, U17.34
!SAFEBOOT!17: !SAFEBOOT!17.1, U18.34
!SAFEBOOT!18: !SAFEBOOT!18.1, U19.34
!SAFEBOOT!19: !SAFEBOOT!19.1, U20.34
!SAFEBOOT!20: !SAFEBOOT!20.1, U21.34
!SAFEBOOT!21: !SAFEBOOT!21.1, U22.34
!SAFEBOOT!22: !SAFEBOOT!22.1, U23.34
!SAFEBOOT!23: !SAFEBOOT!23.1, U24.34
!SAFEBOOT!24: !SAFEBOOT!24.1, U25.34
!SAFEBOOT!25: !SAFEBOOT!25.1, U26.34
!SAFEBOOT!26: !SAFEBOOT!26.1, U27.34
!SAFEBOOT!27: !SAFEBOOT!27.1, U28.34
!SAFEBOOT!28: !SAFEBOOT!28.1, U29.34
!SAFEBOOT!29: !SAFEBOOT!29.1, U30.34
!SAFEBOOT!30: !SAFEBOOT!30.1, U31.34
!SAFEBOOT!31: !SAFEBOOT!31.1, U32.34
!SAFEBOOT!32: !SAFEBOOT!32.1, U33.34
!SAFEBOOT!33: !SAFEBOOT!33.1, U34.34
!SAFEBOOT!34: !SAFEBOOT!34.1, U35.34
!SAFEBOOT!35: !SAFEBOOT!35.1, U36.34
!SAFEBOOT!36: !SAFEBOOT!36.1, U37.34
!SAFEBOOT!37: !SAFEBOOT!37.1, U38.34
!SAFEBOOT!38: !SAFEBOOT!38.1, U39.34
!SAFEBOOT!39: !SAFEBOOT!39.1, U40.34
!SAFEBOOT!40: !SAFEBOOT!40.1, U41.34
!SAFEBOOT!41: !SAFEBOOT!41.1, U42.34
!SAFEBOOT!42: !SAFEBOOT!42.1, U43.34
!SAFEBOOT!43: !SAFEBOOT!43.1, U44.34
!SAFEBOOT!44: !SAFEBOOT!44.1, U45.34
!SAFEBOOT!45: !SAFEBOOT!45.1, U46.34
!SAFEBOOT!46: !SAFEBOOT!46.1, U47.34
!SAFEBOOT!47: !SAFEBOOT!47.1, U48.34
ANT: D2.2, FB1.1, J4.FEED, U1.4
ANT1: D4.2, FB2.1, J1.FEED, U2.4
ANT2: D6.2, FB3.1, J2.FEED, U3.4
ANT3: D8.2, FB4.1, J3.FEED, U4.4
ANT4: D10.2, FB5.1, J5.FEED, U5.4
ANT5: D12.2, FB6.1, J6.FEED, U6.4
ANT6: D14.2, FB7.1, J7.FEED, U7.4
ANT7: D16.2, FB8.1, J8.FEED, U8.4
ANT8: D18.2, FB9.1, J9.FEED, U9.4
ANT9: D20.2, FB10.1, J10.FEED, U10.4
ANT10: D22.2, FB11.1, J11.FEED, U11.4
ANT11: D24.2, FB12.1, J12.FEED, U12.4
ANT12: D26.2, FB13.1, J13.FEED, U13.4
ANT13: D28.2, FB14.1, J14.FEED, U14.4
ANT14: D30.2, FB15.1, J15.FEED, U15.4
ANT15: D32.2, FB16.1, J16.FEED, U16.4
ANT16: D34.2, FB17.1, J17.FEED, U17.4
ANT17: D36.2, FB18.1, J18.FEED, U18.4
ANT18: D38.2, FB19.1, J19.FEED, U19.4
ANT19: D40.2, FB20.1, J20.FEED, U20.4
ANT20: D42.2, FB21.1, J21.FEED, U21.4
ANT21: D44.2, FB22.1, J22.FEED, U22.4
ANT22: D46.2, FB23.1, J23.FEED, U23.4
ANT23: D48.2, FB24.1, J24.FEED, U24.4
ANT24: D50.2, FB25.1, J25.FEED, U25.4
ANT25: D52.2, FB26.1, J26.FEED, U26.4
ANT26: D54.2, FB27.1, J27.FEED, U27.4
ANT27: D56.2, FB28.1, J28.FEED, U28.4
ANT28: D58.2, FB29.1, J29.FEED, U29.4
ANT29: D60.2, FB30.1, J30.FEED, U30.4
ANT30: D62.2, FB31.1, J31.FEED, U31.4
ANT31: D64.2, FB32.1, J32.FEED, U32.4
ANT32: D66.2, FB33.1, J33.FEED, U33.4
ANT33: D68.2, FB34.1, J34.FEED, U34.4
ANT34: D70.2, FB35.1, J35.FEED, U35.4
ANT35: D72.2, FB36.1, J36.FEED, U36.4
ANT36: D74.2, FB37.1, J37.FEED, U37.4
ANT37: D76.2, FB38.1, J38.FEED, U38.4
ANT38: D78.2, FB39.1, J39.FEED, U39.4
ANT39: D80.2, FB40.1, J40.FEED, U40.4
ANT40: D82.2, FB41.1, J41.FEED, U41.4
ANT41: D84.2, FB42.1, J42.FEED, U42.4
ANT42: D86.2, FB43.1, J43.FEED, U43.4
ANT43: D88.2, FB44.1, J44.FEED, U44.4
ANT44: D90.2, FB45.1, J45.FEED, U45.4
ANT45: D92.2, FB46.1, J46.FEED, U46.4
ANT46: D94.2, FB47.1, J47.FEED, U47.4
ANT47: D96.2, FB48.1, J48.FEED, U48.4
CIPO: IN.6, OUT.6
CIPO1: IN1.6, OUT1.6
CIPO2: IN2.6, OUT2.6
CIPO3: IN3.6, OUT3.6
CIPO4: IN4.6, OUT4.6
CIPO5: IN5.6, OUT5.6
CIPO6: IN6.6, OUT6.6
CIPO7: IN7.6, OUT7.6
CIPO8: IN8.6, OUT8.6
CIPO9: IN9.6, OUT9.6
CIPO10: IN10.6, OUT10.6
CIPO11: IN11.6, OUT11.6
CIPO12: IN12.6, OUT12.6
CIPO13: IN13.6, OUT13.6
CIPO14: IN14.6, OUT14.6
CIPO15: IN15.6, OUT15.6
CIPO16: IN16.6, OUT16.6
CIPO17: IN17.6, OUT17.6
CIPO18: IN18.6, OUT18.6
CIPO19: IN19.6, OUT19.6
CIPO20: IN20.6, OUT20.6
CIPO21: IN21.6, OUT21.6
CIPO22: IN22.6, OUT22.6
CIPO23: IN23.6, OUT23.6
CIPO24: IN24.6, OUT24.6
CIPO25: IN25.6, OUT25.6
CIPO26: IN26.6, OUT26.6
CIPO27: IN27.6, OUT27.6
CIPO28: IN28.6, OUT28.6
CIPO29: IN29.6, OUT29.6
CIPO30: IN30.6, OUT30.6
CIPO31: IN31.6, OUT31.6
CIPO32: IN32.6, OUT32.6
CIPO33: IN33.6, OUT33.6
CIPO34: IN34.6, OUT34.6
CIPO35: IN35.6, OUT35.6
CIPO36: IN36.6, OUT36.6
CIPO37: IN37.6, OUT37.6
CIPO38: IN38.6, OUT38.6
CIPO39: IN39.6, OUT39.6
CIPO40: IN40.6, OUT40.6
CIPO41: IN41.6, OUT41.6
CIPO42: IN42.6, OUT42.6
CIPO43: IN43.6, OUT43.6
CIPO44: IN44.6, OUT44.6
CIPO45: IN45.6, OUT45.6
CIPO46: IN46.6, OUT46.6
CIPO47: IN47.6, OUT47.6
COPI: IN.5, OUT.5
COPI1: IN1.5, OUT1.5
COPI2: IN2.5, OUT2.5
COPI3: IN3.5, OUT3.5
COPI4: IN4.5, OUT4.5
COPI5: IN5.5, OUT5.5
COPI6: IN6.5, OUT6.5
COPI7: IN7.5, OUT7.5
COPI8: IN8.5, OUT8.5
COPI9: IN9.5, OUT9.5
COPI10: IN10.5, OUT10.5
COPI11: IN11.5, OUT11.5
COPI12: IN12.5, OUT12.5
COPI13: IN13.5, OUT13.5
COPI14: IN14.5, OUT14.5
COPI15: IN15.5, OUT15.5
COPI16: IN16.5, OUT16.5
COPI17: IN17.5, OUT17.5
COPI18: IN18.5, OUT18.5
COPI19: IN19.5, OUT19.5
COPI20: IN20.5, OUT20.5
COPI21: IN21.5, OUT21.5
COPI22: IN22.5, OUT22.5
COPI23: IN23.5, OUT23.5
COPI24: IN24.5, OUT24.5
COPI25: IN25.5, OUT25.5
COPI26: IN26.5, OUT26.5
COPI27: IN27.5, OUT27.5
COPI28: IN28.5, OUT28.5
COPI29: IN29.5, OUT29.5
COPI30: IN30.5, OUT30.5
COPI31: IN31.5, OUT31.5
COPI32: IN32.5, OUT32.5
COPI33: IN33.5, OUT33.5
COPI34: IN34.5, OUT34.5
COPI35: IN35.5, OUT35.5
COPI36: IN36.5, OUT36.5
COPI37: IN37.5, OUT37.5
COPI38: IN38.5, OUT38.5
COPI39: IN39.5, OUT39.5
COPI40: IN40.5, OUT40.5
COPI41: IN41.5, OUT41.5
COPI42: IN42.5, OUT42.5
COPI43: IN43.5, OUT43.5
COPI44: IN44.5, OUT44.5
COPI45: IN45.5, OUT45.5
COPI46: IN46.5, OUT46.5
COPI47: IN47.5, OUT47.5
CS0: IN.7, OUT.7
CS1: IN.8, OUT.8
CS2: IN.9, OUT.9
CS3: IN1.7, OUT1.7
CS4: IN1.8, OUT1.8
CS5: IN1.9, OUT1.9
CS6: IN2.7, OUT2.7
CS7: IN2.8, OUT2.8
CS8: IN2.9, OUT2.9
CS9: IN3.7, OUT3.7
CS10: IN3.8, OUT3.8
CS11: IN3.9, OUT3.9
CS12: IN4.7, OUT4.7
CS13: IN4.8, OUT4.8
CS14: IN4.9, OUT4.9
CS15: IN5.7, OUT5.7
CS16: IN5.8, OUT5.8
CS17: IN5.9, OUT5.9
CS18: IN6.7, OUT6.7
CS19: IN6.8, OUT6.8
CS20: IN6.9, OUT6.9
CS21: IN7.7, OUT7.7
CS22: IN7.8, OUT7.8
CS23: IN7.9, OUT7.9
CS24: IN8.7, OUT8.7
CS25: IN8.8, OUT8.8
CS26: IN8.9, OUT8.9
CS27: IN9.7, OUT9.7
CS28: IN9.8, OUT9.8
CS29: IN9.9, OUT9.9
CS30: IN10.7, OUT10.7
CS31: IN10.8, OUT10.8
CS32: IN10.9, OUT10.9
CS33: IN11.7, OUT11.7
CS34: IN11.8, OUT11.8
CS35: IN11.9, OUT11.9
CS36: IN12.7, OUT12.7
CS37: IN12.8, OUT12.8
CS38: IN12.9, OUT12.9
CS39: IN13.7, OUT13.7
CS40: IN13.8, OUT13.8
CS41: IN13.9, OUT13.9
CS42: IN14.7, OUT14.7
CS43: IN14.8, OUT14.8
CS44: IN14.9, OUT14.9
CS45: IN15.7, OUT15.7
CS46: IN15.8, OUT15.8
CS47: IN15.9, OUT15.9
CS48: IN16.7, OUT16.7
CS49: IN16.8, OUT16.8
CS50: IN16.9, OUT16.9
CS51: IN17.7, OUT17.7
CS52: IN17.8, OUT17.8
CS53: IN17.9, OUT17.9
CS54: IN18.7, OUT18.7
CS55: IN18.8, OUT18.8
CS56: IN18.9, OUT18.9
CS57: IN19.7, OUT19.7
CS58: IN19.8, OUT19.8
CS59: IN19.9, OUT19.9
CS60: IN20.7, OUT20.7
CS61: IN20.8, OUT20.8
CS62: IN20.9, OUT20.9
CS63: IN21.7, OUT21.7
CS64: IN21.8, OUT21.8
CS65: IN21.9, OUT21.9
CS66: IN22.7, OUT22.7
CS67: IN22.8, OUT22.8
CS68: IN22.9, OUT22.9
CS69: IN23.7, OUT23.7
CS70: IN23.8, OUT23.8
CS71: IN23.9, OUT23.9
CS72: IN24.7, OUT24.7
CS73: IN24.8, OUT24.8
CS74: IN24.9, OUT24.9
CS75: IN25.7, OUT25.7
CS76: IN25.8, OUT25.8
CS77: IN25.9, OUT25.9
CS78: IN26.7, OUT26.7
CS79: IN26.8, OUT26.8
CS80: IN26.9, OUT26.9
CS81: IN27.7, OUT27.7
CS82: IN27.8, OUT27.8
CS83: IN27.9, OUT27.9
CS84: IN28.7, OUT28.7
CS85: IN28.8, OUT28.8
CS86: IN28.9, OUT28.9
CS87: IN29.7, OUT29.7
CS88: IN29.8, OUT29.8
CS89: IN29.9, OUT29.9
CS90: IN30.7, OUT30.7
CS91: IN30.8, OUT30.8
CS92: IN30.9, OUT30.9
CS93: IN31.7, OUT31.7
CS94: IN31.8, OUT31.8
CS95: IN31.9, OUT31.9
CS96: IN32.7, OUT32.7
CS97: IN32.8, OUT32.8
CS98: IN32.9, OUT32.9
CS99: IN33.7, OUT33.7
CS100: IN33.8, OUT33.8
CS101: IN33.9, OUT33.9
CS102: IN34.7, OUT34.7
CS103: IN34.8, OUT34.8
CS104: IN34.9, OUT34.9
CS105: IN35.7, OUT35.7
CS106: IN35.8, OUT35.8
CS107: IN35.9, OUT35.9
CS108: IN36.7, OUT36.7
CS109: IN36.8, OUT36.8
CS110: IN36.9, OUT36.9
CS111: IN37.7, OUT37.7
CS112: IN37.8, OUT37.8
CS113: IN37.9, OUT37.9
CS114: IN38.7, OUT38.7
CS115: IN38.8, OUT38.8
CS116: IN38.9, OUT38.9
CS117: IN39.7, OUT39.7
CS118: IN39.8, OUT39.8
CS119: IN39.9, OUT39.9
CS120: IN40.7, OUT40.7
CS121: IN40.8, OUT40.8
CS122: IN40.9, OUT40.9
CS123: IN41.7, OUT41.7
CS124: IN41.8, OUT41.8
CS125: IN41.9, OUT41.9
CS126: IN42.7, OUT42.7
CS127: IN42.8, OUT42.8
CS128: IN42.9, OUT42.9
CS129: IN43.7, OUT43.7
CS130: IN43.8, OUT43.8
CS131: IN43.9, OUT43.9
CS132: IN44.7, OUT44.7
CS133: IN44.8, OUT44.8
CS134: IN44.9, OUT44.9
CS135: IN45.7, OUT45.7
CS136: IN45.8, OUT45.8
CS137: IN45.9, OUT45.9
CS138: IN46.7, OUT46.7
CS139: IN46.8, OUT46.8
CS140: IN46.9, OUT46.9
CS141: IN47.7, OUT47.7
CS142: IN47.8, OUT47.8
CS143: IN47.9, OUT47.9
GND: B1.-, C1.2, C2.2, C3.2, C4.2, C5.2, C6.2, C8.2, C9.2, C10.2, C11.2, D2.1, IN.3, IN.14, J4.1, J4.2, OUT.3, OUT.14, U1.1, U1.3, U1.5, U1.7, U1.8, U1.9, U1.10, U1.11, U1.12, U1.17, U1.23, U1.29, U1.31, U1.37, U1.38, U1.39, U1.40, U1.41, U1.44, U1.46, U1.47, U1.49
GND1: B2.-, C7.2, C12.2, C13.2, C14.2, C15.2, C16.2, C17.2, C18.2, C19.2, C20.2, D4.1, IN1.3, IN1.14, J1.1, J1.2, OUT1.3, OUT1.14, U2.1, U2.3, U2.5, U2.7, U2.8, U2.9, U2.10, U2.11, U2.12, U2.17, U2.23, U2.29, U2.31, U2.37, U2.38, U2.39, U2.40, U2.41, U2.44, U2.46, U2.47, U2.49
GND2: B3.-, C21.2, C22.2, C23.2, C24.2, C25.2, C26.2, C27.2, C28.2, C29.2, C30.2, D6.1, IN2.3, IN2.14, J2.1, J2.2, OUT2.3, OUT2.14, U3.1, U3.3, U3.5, U3.7, U3.8, U3.9, U3.10, U3.11, U3.12, U3.17, U3.23, U3.29, U3.31, U3.37, U3.38, U3.39, U3.40, U3.41, U3.44, U3.46, U3.47, U3.49
GND3: B4.-, C31.2, C32.2, C33.2, C34.2, C35.2, C36.2, C37.2, C38.2, C39.2, C40.2, D8.1, IN3.3, IN3.14, J3.1, J3.2, OUT3.3, OUT3.14, U4.1, U4.3, U4.5, U4.7, U4.8, U4.9, U4.10, U4.11, U4.12, U4.17, U4.23, U4.29, U4.31, U4.37, U4.38, U4.39, U4.40, U4.41, U4.44, U4.46, U4.47, U4.49
GND4: B5.-, C41.2, C42.2, C43.2, C44.2, C45.2, C46.2, C47.2, C48.2, C49.2, C50.2, D10.1, IN4.3, IN4.14, J5.1, J5.2, OUT4.3, OUT4.14, U5.1, U5.3, U5.5, U5.7, U5.8, U5.9, U5.10, U5.11, U5.12, U5.17, U5.23, U5.29, U5.31, U5.37, U5.38, U5.39, U5.40, U5.41, U5.44, U5.46, U5.47, U5.49
GND5: B6.-, C51.2, C52.2, C53.2, C54.2, C55.2, C56.2, C57.2, C58.2, C59.2, C60.2, D12.1, IN5.3, IN5.14, J6.1, J6.2, OUT5.3, OUT5.14, U6.1, U6.3, U6.5, U6.7, U6.8, U6.9, U6.10, U6.11, U6.12, U6.17, U6.23, U6.29, U6.31, U6.37, U6.38, U6.39, U6.40, U6.41, U6.44, U6.46, U6.47, U6.49
GND6: B7.-, C61.2, C62.2, C63.2, C64.2, C65.2, C66.2, C67.2, C68.2, C69.2, C70.2, D14.1, IN6.3, IN6.14, J7.1, J7.2, OUT6.3, OUT6.14, U7.1, U7.3, U7.5, U7.7, U7.8, U7.9, U7.10, U7.11, U7.12, U7.17, U7.23, U7.29, U7.31, U7.37, U7.38, U7.39, U7.40, U7.41, U7.44, U7.46, U7.47, U7.49
GND7: B8.-, C71.2, C72.2, C73.2, C74.2, C75.2, C76.2, C77.2, C78.2, C79.2, C80.2, D16.1, IN7.3, IN7.14, J8.1, J8.2, OUT7.3, OUT7.14, U8.1, U8.3, U8.5, U8.7, U8.8, U8.9, U8.10, U8.11, U8.12, U8.17, U8.23, U8.29, U8.31, U8.37, U8.38, U8.39, U8.40, U8.41, U8.44, U8.46, U8.47, U8.49
GND8: B9.-, C81.2, C82.2, C83.2, C84.2, C85.2, C86.2, C87.2, C88.2, C89.2, C90.2, D18.1, IN8.3, IN8.14, J9.1, J9.2, OUT8.3, OUT8.14, U9.1, U9.3, U9.5, U9.7, U9.8, U9.9, U9.10, U9.11, U9.12, U9.17, U9.23, U9.29, U9.31, U9.37, U9.38, U9.39, U9.40, U9.41, U9.44, U9.46, U9.47, U9.49
GND9: B10.-, C91.2, C92.2, C93.2, C94.2, C95.2, C96.2, C97.2, C98.2, C99.2, C100.2, D20.1, IN9.3, IN9.14, J10.1, J10.2, OUT9.3, OUT9.14, U10.1, U10.3, U10.5, U10.7, U10.8, U10.9, U10.10, U10.11, U10.12, U10.17, U10.23, U10.29, U10.31, U10.37, U10.38, U10.39, U10.40, U10.41, U10.44, U10.46, U10.47, U10.49
GND10: B11.-, C101.2, C102.2, C103.2, C104.2, C105.2, C106.2, C107.2, C108.2, C109.2, C110.2, D22.1, IN10.3, IN10.14, J11.1, J11.2, OUT10.3, OUT10.14, U11.1, U11.3, U11.5, U11.7, U11.8, U11.9, U11.10, U11.11, U11.12, U11.17, U11.23, U11.29, U11.31, U11.37, U11.38, U11.39, U11.40, U11.41, U11.44, U11.46, U11.47, U11.49
GND11: B12.-, C111.2, C112.2, C113.2, C114.2, C115.2, C116.2, C117.2, C118.2, C119.2, C120.2, D24.1, IN11.3, IN11.14, J12.1, J12.2, OUT11.3, OUT11.14, U12.1, U12.3, U12.5, U12.7, U12.8, U12.9, U12.10, U12.11, U12.12, U12.17, U12.23, U12.29, U12.31, U12.37, U12.38, U12.39, U12.40, U12.41, U12.44, U12.46, U12.47, U12.49
GND12: B13.-, C121.2, C122.2, C123.2, C124.2, C125.2, C126.2, C127.2, C128.2, C129.2, C130.2, D26.1, IN12.3, IN12.14, J13.1, J13.2, OUT12.3, OUT12.14, U13.1, U13.3, U13.5, U13.7, U13.8, U13.9, U13.10, U13.11, U13.12, U13.17, U13.23, U13.29, U13.31, U13.37, U13.38, U13.39, U13.40, U13.41, U13.44, U13.46, U13.47, U13.49
GND13: B14.-, C131.2, C132.2, C133.2, C134.2, C135.2, C136.2, C137.2, C138.2, C139.2, C140.2, D28.1, IN13.3, IN13.14, J14.1, J14.2, OUT13.3, OUT13.14, U14.1, U14.3, U14.5, U14.7, U14.8, U14.9, U14.10, U14.11, U14.12, U14.17, U14.23, U14.29, U14.31, U14.37, U14.38, U14.39, U14.40, U14.41, U14.44, U14.46, U14.47, U14.49
GND14: B15.-, C141.2, C142.2, C143.2, C144.2, C145.2, C146.2, C147.2, C148.2, C149.2, C150.2, D30.1, IN14.3, IN14.14, J15.1, J15.2, OUT14.3, OUT14.14, U15.1, U15.3, U15.5, U15.7, U15.8, U15.9, U15.10, U15.11, U15.12, U15.17, U15.23, U15.29, U15.31, U15.37, U15.38, U15.39, U15.40, U15.41, U15.44, U15.46, U15.47, U15.49
GND15: B16.-, C151.2, C152.2, C153.2, C154.2, C155.2, C156.2, C157.2, C158.2, C159.2, C160.2, D32.1, IN15.3, IN15.14, J16.1, J16.2, OUT15.3, OUT15.14, U16.1, U16.3, U16.5, U16.7, U16.8, U16.9, U16.10, U16.11, U16.12, U16.17, U16.23, U16.29, U16.31, U16.37, U16.38, U16.39, U16.40, U16.41, U16.44, U16.46, U16.47, U16.49
GND16: B17.-, C161.2, C162.2, C163.2, C164.2, C165.2, C166.2, C167.2, C168.2, C169.2, C170.2, D34.1, IN16.3, IN16.14, J17.1, J17.2, OUT16.3, OUT16.14, U17.1, U17.3, U17.5, U17.7, U17.8, U17.9, U17.10, U17.11, U17.12, U17.17, U17.23, U17.29, U17.31, U17.37, U17.38, U17.39, U17.40, U17.41, U17.44, U17.46, U17.47, U17.49
GND17: B18.-, C171.2, C172.2, C173.2, C174.2, C175.2, C176.2, C177.2, C178.2, C179.2, C180.2, D36.1, IN17.3, IN17.14, J18.1, J18.2, OUT17.3, OUT17.14, U18.1, U18.3, U18.5, U18.7, U18.8, U18.9, U18.10, U18.11, U18.12, U18.17, U18.23, U18.29, U18.31, U18.37, U18.38, U18.39, U18.40, U18.41, U18.44, U18.46, U18.47, U18.49
GND18: B19.-, C181.2, C182.2, C183.2, C184.2, C185.2, C186.2, C187.2, C188.2, C189.2, C190.2, D38.1, IN18.3, IN18.14, J19.1, J19.2, OUT18.3, OUT18.14, U19.1, U19.3, U19.5, U19.7, U19.8, U19.9, U19.10, U19.11, U19.12, U19.17, U19.23, U19.29, U19.31, U19.37, U19.38, U19.39, U19.40, U19.41, U19.44, U19.46, U19.47, U19.49
GND19: B20.-, C191.2, C192.2, C193.2, C194.2, C195.2, C196.2, C197.2, C198.2, C199.2, C200.2, D40.1, IN19.3, IN19.14, J20.1, J20.2, OUT19.3, OUT19.14, U20.1, U20.3, U20.5, U20.7, U20.8, U20.9, U20.10, U20.11, U20.12, U20.17, U20.23, U20.29, U20.31, U20.37, U20.38, U20.39, U20.40, U20.41, U20.44, U20.46, U20.47, U20.49
GND20: B21.-, C201.2, C202.2, C203.2, C204.2, C205.2, C206.2, C207.2, C208.2, C209.2, C210.2, D42.1, IN20.3, IN20.14, J21.1, J21.2, OUT20.3, OUT20.14, U21.1, U21.3, U21.5, U21.7, U21.8, U21.9, U21.10, U21.11, U21.12, U21.17, U21.23, U21.29, U21.31, U21.37, U21.38, U21.39, U21.40, U21.41, U21.44, U21.46, U21.47, U21.49
GND21: B22.-, C211.2, C212.2, C213.2, C214.2, C215.2, C216.2, C217.2, C218.2, C219.2, C220.2, D44.1, IN21.3, IN21.14, J22.1, J22.2, OUT21.3, OUT21.14, U22.1, U22.3, U22.5, U22.7, U22.8, U22.9, U22.10, U22.11, U22.12, U22.17, U22.23, U22.29, U22.31, U22.37, U22.38, U22.39, U22.40, U22.41, U22.44, U22.46, U22.47, U22.49
GND22: B23.-, C221.2, C222.2, C223.2, C224.2, C225.2, C226.2, C227.2, C228.2, C229.2, C230.2, D46.1, IN22.3, IN22.14, J23.1, J23.2, OUT22.3, OUT22.14, U23.1, U23.3, U23.5, U23.7, U23.8, U23.9, U23.10, U23.11, U23.12, U23.17, U23.23, U23.29, U23.31, U23.37, U23.38, U23.39, U23.40, U23.41, U23.44, U23.46, U23.47, U23.49
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
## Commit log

2021-05-04 Review updates
2021-05-04 Adding production panel
2021-05-27 Gapless production panel
2021-06-09 Update 16-way FPC Connector
2021-07-30 Change R2 to RES-15724
2021-08-19 Add smôl branding
2021-08-20 Change EZ to smôl on schematic
2021-10-28 Add SKU and product image
2022-04-07 Update schematic
